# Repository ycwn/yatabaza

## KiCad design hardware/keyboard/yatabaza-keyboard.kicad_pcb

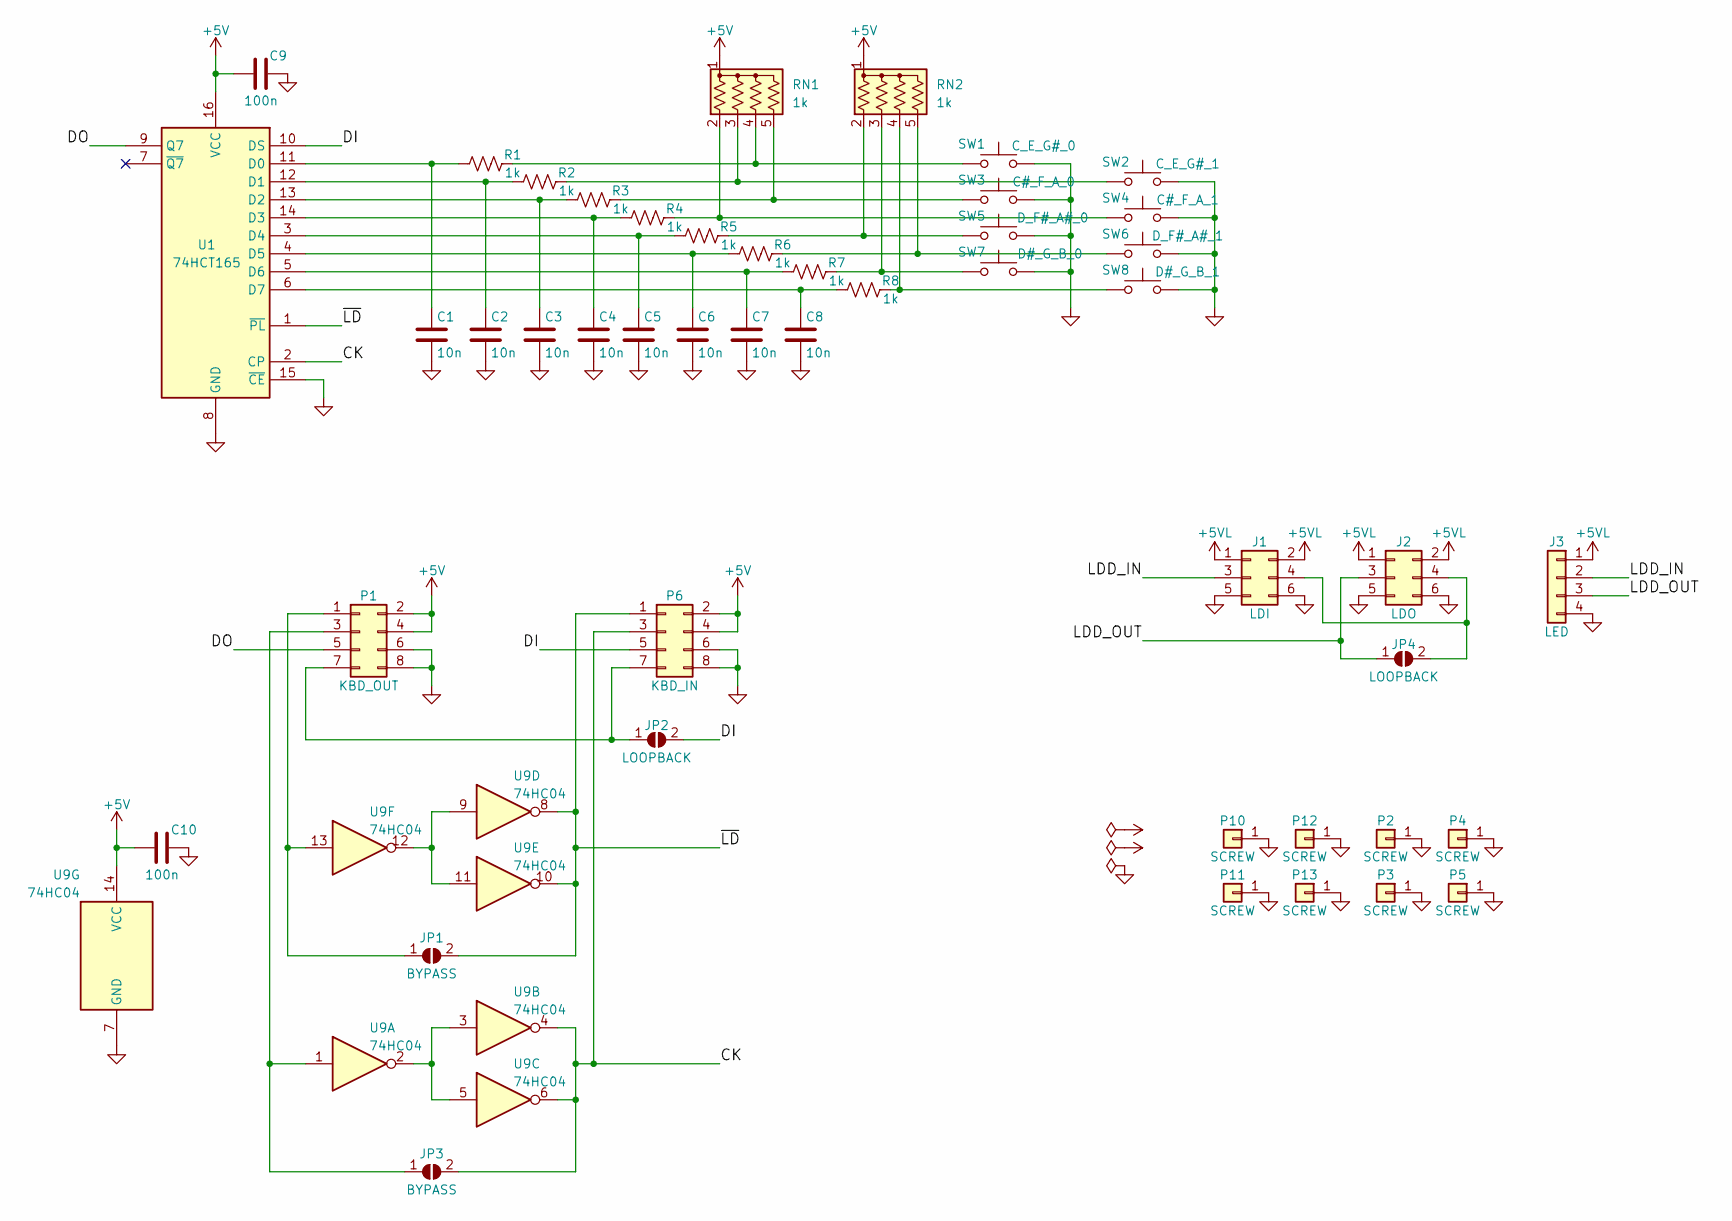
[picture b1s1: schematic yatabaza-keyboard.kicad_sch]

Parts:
C1, C2, C3, C4, C5, C6, C7, C8: 10n; C_Disc_D3.0mm_W1.6mm_P2.50mm
C9, C10: 100n; C_Disc_D3.0mm_W1.6mm_P2.50mm
J1: LDI; PinHeader_2x03_P2.54mm_Vertical
J2: LDO; PinHeader_2x03_P2.54mm_Vertical
J3: LED; PinHeader_1x04_P2.54mm_Vertical
JP1, JP3: BYPASS; SolderJumper-2_P1.3mm_Open_Pad1.0x1.5mm
JP2, JP4: LOOPBACK; SolderJumper-2_P1.3mm_Open_Pad1.0x1.5mm
P1: KBD_OUT; PinHeader_2x04_P2.54mm_Vertical
P2, P3, P4, P5, P10, P11, P12, P13: SCREW; MountingHole_3.5mm_Pad
P6: KBD_IN; PinHeader_2x04_P2.54mm_Vertical
R1, R2, R3, R4, R5, R6, R7, R8: 1k; R_Axial_DIN0204_L3.6mm_D1.6mm_P2.54mm_Vertical
RN1, RN2: 1k; R_Array_SIP5
SW1: C_E_G#_0; SW_PUSH-12mm
SW2: C_E_G#_1; SW_PUSH-12mm
SW3: C#_F_A_0; SW_PUSH-12mm
SW4: C#_F_A_1; SW_PUSH-12mm
SW5: D_F#_A#_0; SW_PUSH-12mm
SW6: D_F#_A#_1; SW_PUSH-12mm
SW7: D#_G_B_0; SW_PUSH-12mm
SW8: D#_G_B_1; SW_PUSH-12mm
U1: 74HCT165; DIP-16_W7.62mm
U9: 74HC04; DIP-14_W7.62mm

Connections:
+5V: C9.1, C10.1, P1.2, P1.4, P6.2, P6.4, RN1.1 (common), RN2.1 (common), U1.16 (VCC), U9.14 (VCC)
+5VL: J1.1, J1.2, J2.1, J2.2, J3.1
/CK: JP3.2 (B), P6.3, U1.2 (CP), U9.4, U9.6
/DI: JP2.2 (B), P6.5, U1.10 (DS)
/DO: P1.5, U1.9 (Q7)
/LDD_IN: J1.3, J3.2
/LDD_OUT: J2.3, J3.3, JP4.1 (A)
/~LD: JP1.2 (B), P6.1, U1.1 (~PL), U9.8, U9.10
GND: C1.2, C2.2, C3.2, C4.2, C5.2, C6.2, C7.2, C8.2, C9.2, C10.2, J1.5, J1.6, J2.5, J2.6, J3.4, P1.6, P1.8, P2.1, P3.1, P4.1, P5.1, P6.6, P6.8, P10.1, P11.1, P12.1, P13.1, SW1.1, SW2.1, SW3.1, SW4.1, SW5.1, SW6.1, SW7.1, SW8.1, U1.8 (GND), U1.15 (~CE), U9.7 (GND)
unnamed: C1.1, R1.2, U1.11 (D0)
unnamed: C2.1, R2.2, U1.12 (D1)
unnamed: C3.1, R3.2, U1.13 (D2)
unnamed: C4.1, R4.2, U1.14 (D3)
unnamed: C5.1, R5.2, U1.3 (D4)
unnamed: C6.1, R6.2, U1.4 (D5)
unnamed: C7.1, R7.2, U1.5 (D6)
unnamed: C8.1, R8.2, U1.6 (D7)
unnamed: J1.4, J2.4, JP4.2 (B)
unnamed: JP1.1 (A), P1.1, U9.13
unnamed: JP2.1 (A), P1.7, P6.7
unnamed: JP3.1 (A), P1.3, U9.1
unnamed: R1.1, RN1.4 (R3), SW1.2
unnamed: R2.1, RN1.3 (R2), SW2.2
unnamed: R3.1, RN1.5 (R4), SW3.2
unnamed: R4.1, RN1.2 (R1), SW4.2
unnamed: R5.1, RN2.2 (R1), SW5.2
unnamed: R6.1, RN2.5 (R4), SW6.2
unnamed: R7.1, RN2.3 (R2), SW7.2
unnamed: R8.1, RN2.4 (R3), SW8.2
unnamed: U9.2, U9.3, U9.5
unnamed: U9.9, U9.11, U9.12

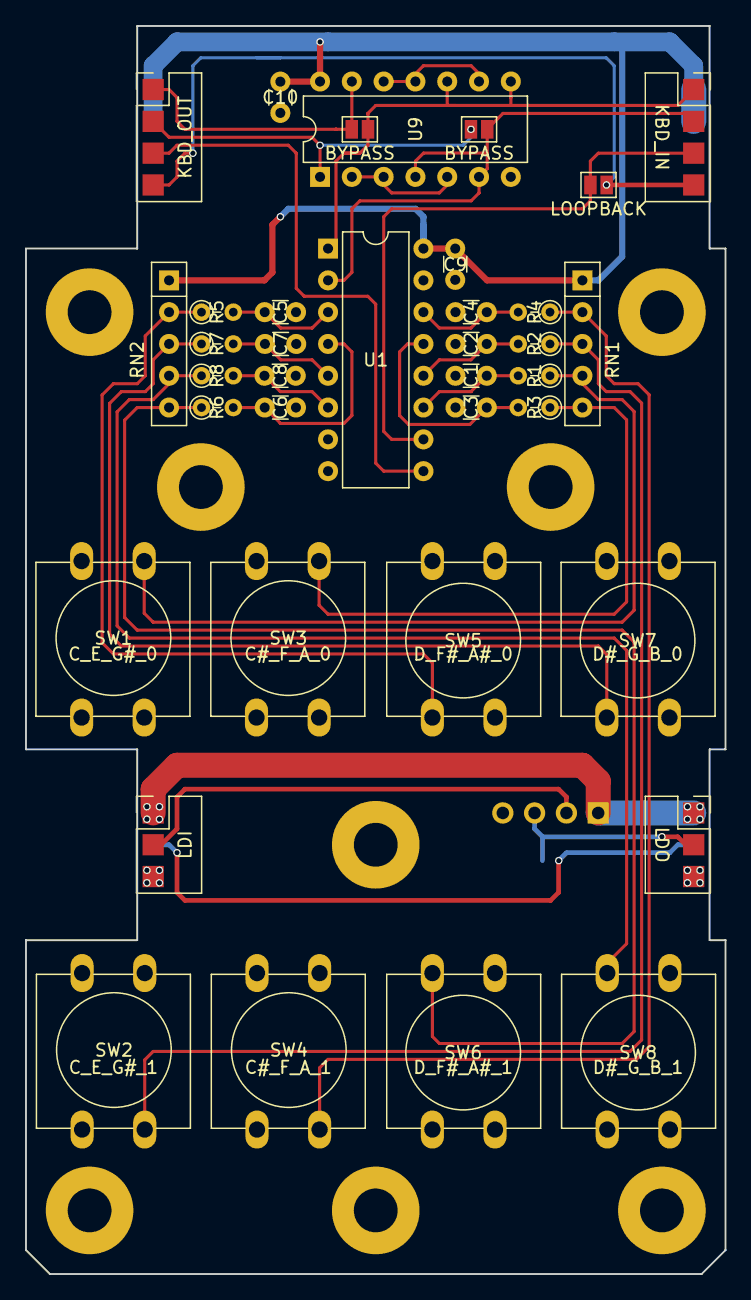
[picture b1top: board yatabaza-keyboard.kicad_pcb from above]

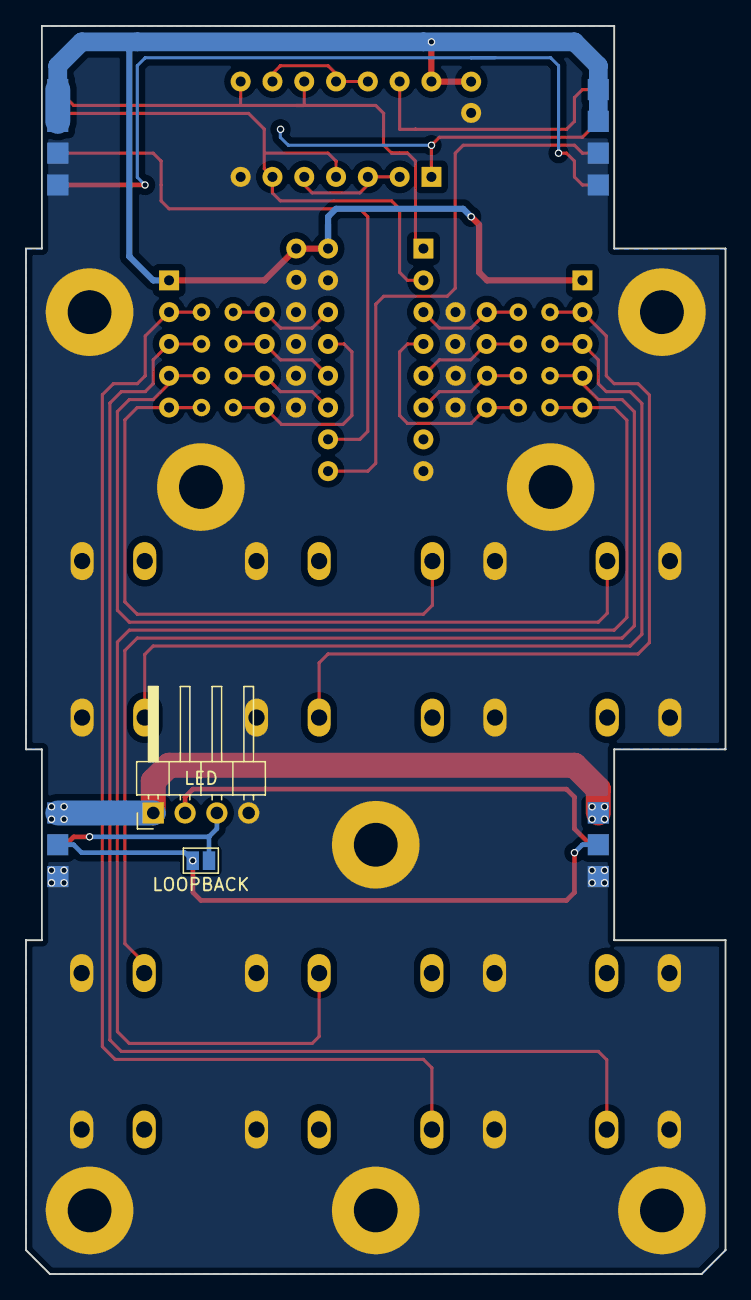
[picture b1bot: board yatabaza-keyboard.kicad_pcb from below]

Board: 2 copper layers, 55.9 x 99.7 mm, 47 parts (2 on the bottom side), 31 nets.

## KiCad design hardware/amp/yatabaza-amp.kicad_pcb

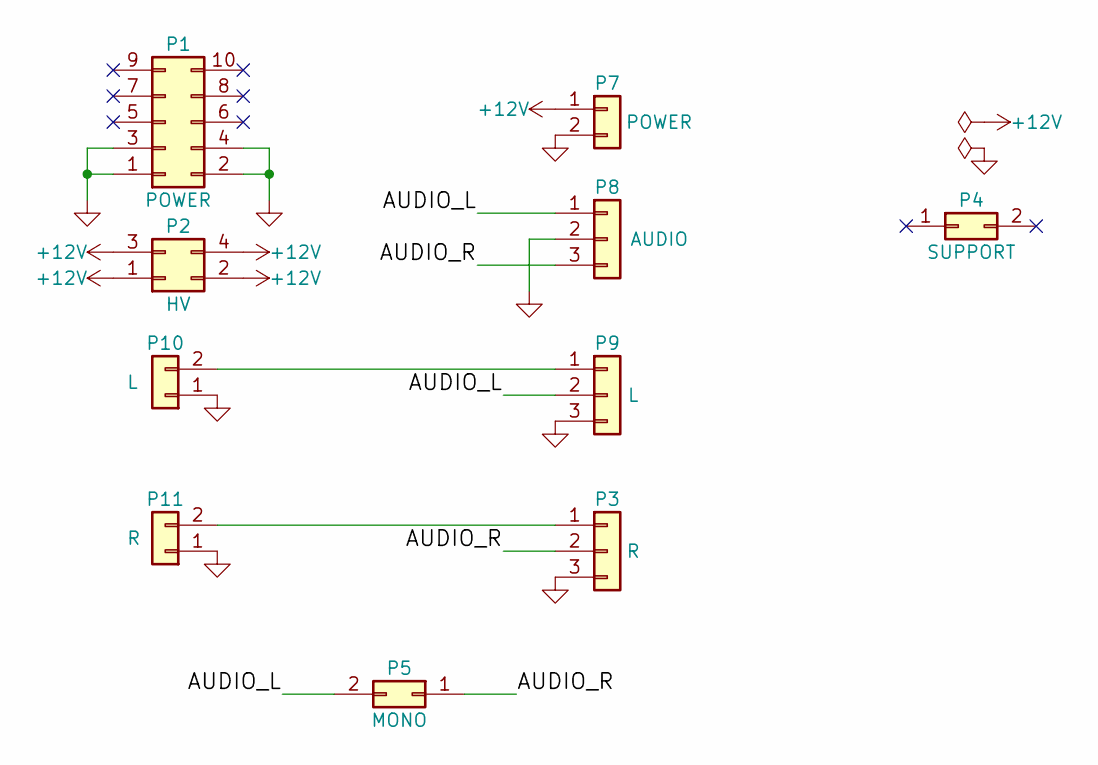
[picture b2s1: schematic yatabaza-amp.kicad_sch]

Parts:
P1: POWER; PinHeader_2x05_P2.54mm_Vertical
P2: HV; PinHeader_2x02_P2.54mm_Vertical
P3: R; PinHeader_1x03_P2.54mm_Vertical
P4: SUPPORT; PinHeader_2x01_P2.54mm_Vertical
P5: MONO; SolderJumper-2_P1.3mm_Open_Pad1.0x1.5mm
P7: POWER; PinHeader_2x01_P2.54mm_Vertical
P8: AUDIO; PinHeader_1x03_P2.54mm_Vertical
P9: L; PinHeader_1x03_P2.54mm_Vertical
P10: L; PinHeader_1x02_P2.54mm_Vertical
P11: R; PinHeader_1x02_P2.54mm_Vertical

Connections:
+12V: P2.1, P2.2, P2.3, P2.4, P7.1
/AUDIO_L: P5.2, P8.1, P9.2
/AUDIO_R: P3.2, P5.1, P8.3
GND: P1.1, P1.2, P1.3, P1.4, P3.3, P7.2, P8.2, P9.3, P10.1, P11.1
unnamed: P3.1, P11.2
unnamed: P9.1, P10.2

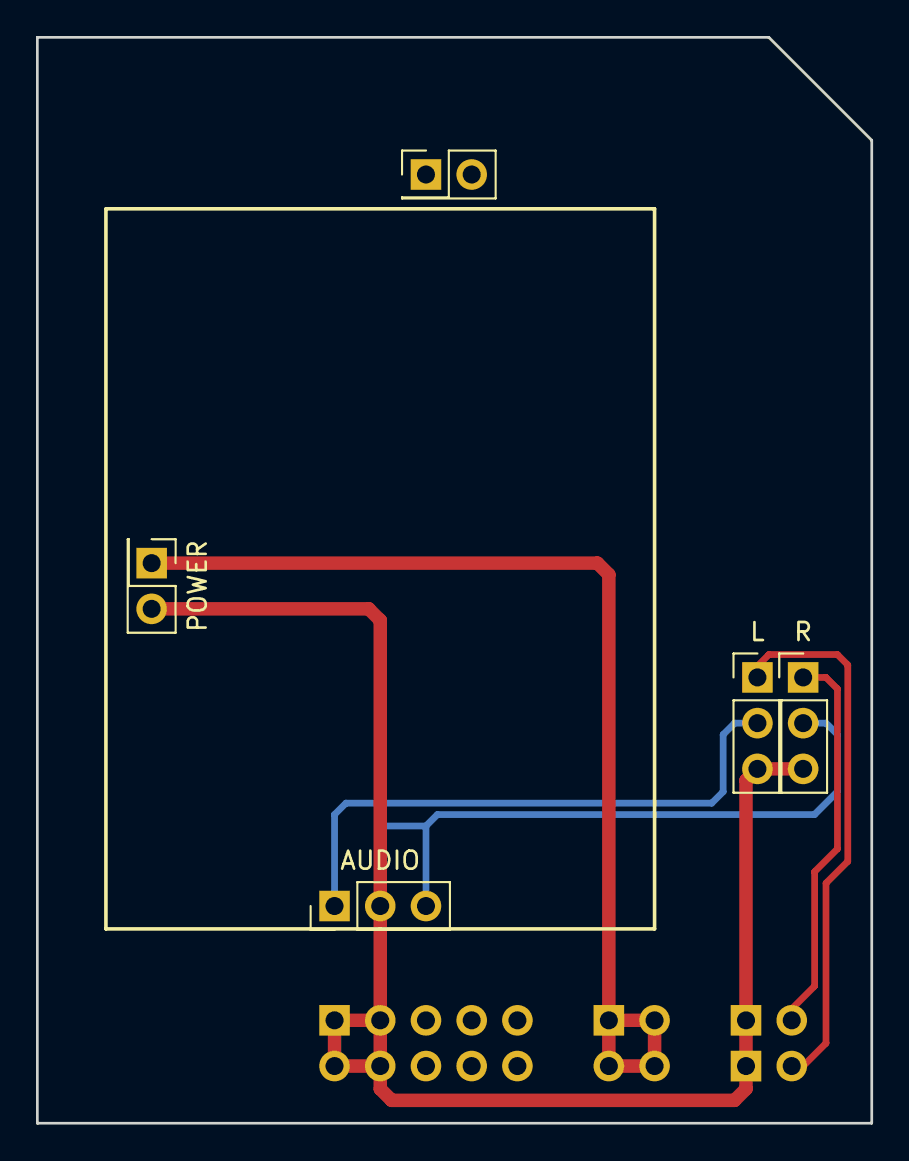
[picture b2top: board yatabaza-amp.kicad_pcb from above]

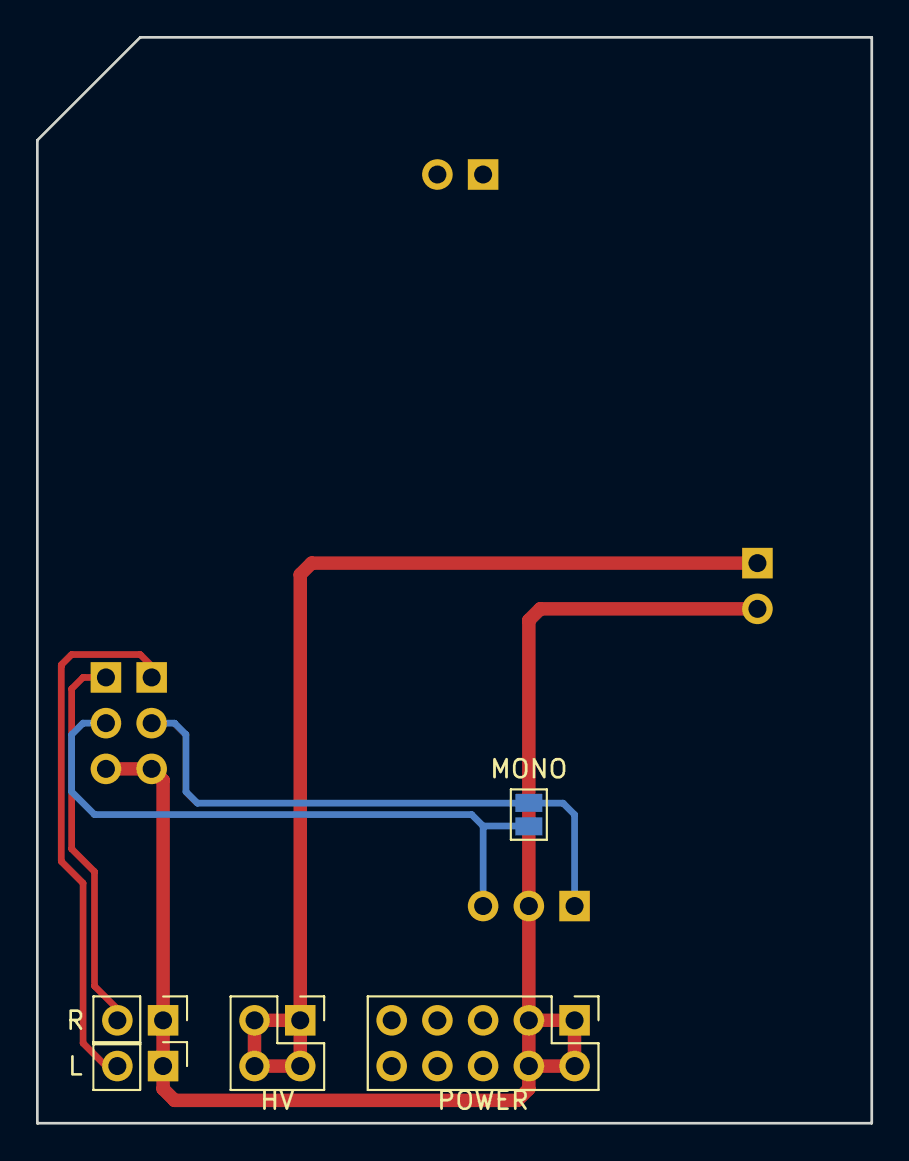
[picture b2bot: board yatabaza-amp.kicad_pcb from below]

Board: 2 copper layers, 46.4 x 60.3 mm, 10 parts (5 on the bottom side), 6 nets.

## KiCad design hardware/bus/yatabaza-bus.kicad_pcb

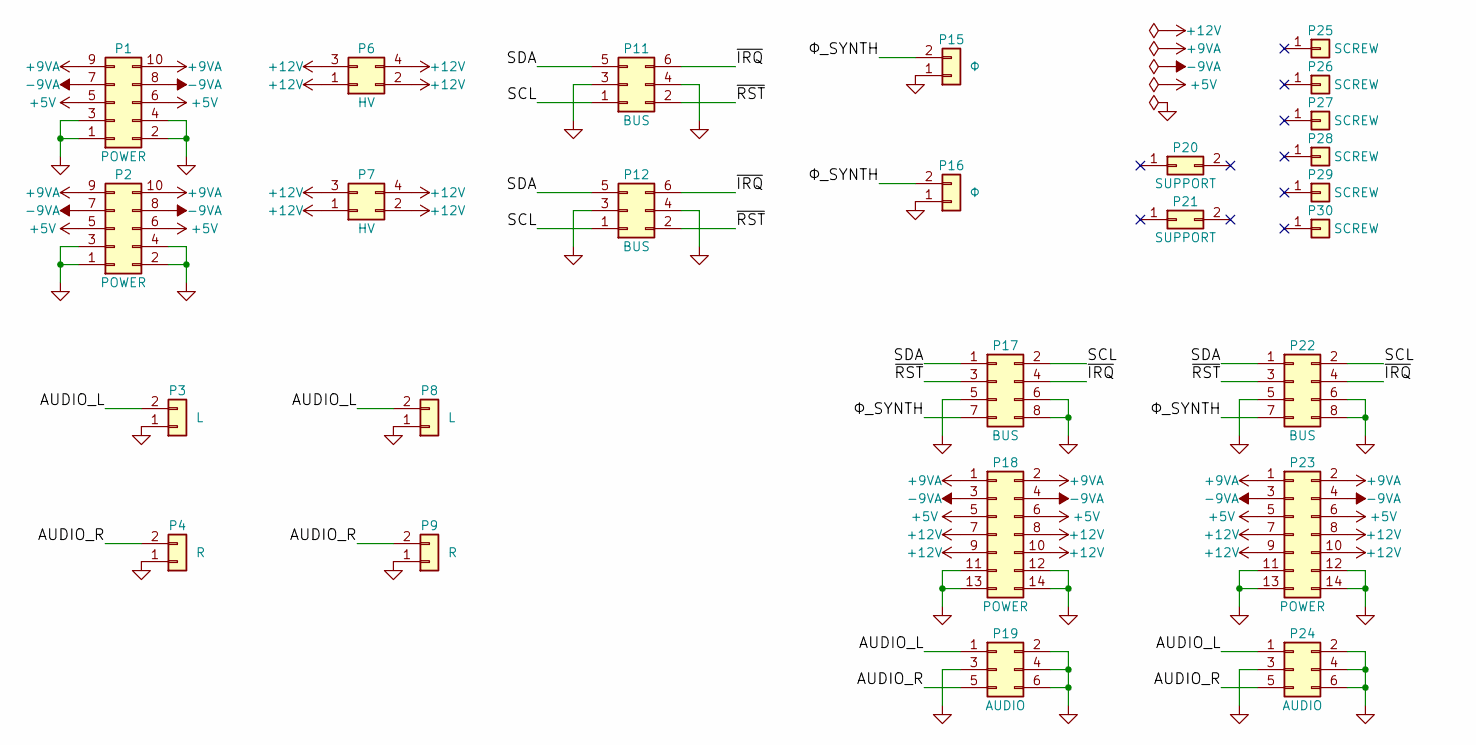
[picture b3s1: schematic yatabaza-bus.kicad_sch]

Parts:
P1, P2: POWER; PinHeader_2x05_P2.54mm_Vertical
P3, P8: L; PinHeader_1x02_P2.54mm_Vertical
P4, P9: R; PinHeader_1x02_P2.54mm_Vertical
P6, P7: HV; PinHeader_2x02_P2.54mm_Vertical
P11, P12: BUS; PinHeader_2x03_P2.54mm_Vertical
P15, P16: Φ; PinHeader_1x02_P2.54mm_Vertical
P17, P22: BUS; PinHeader_2x04_P2.54mm_Vertical
P18, P23: POWER; PinHeader_2x07_P2.54mm_Vertical
P19, P24: AUDIO; PinHeader_2x03_P2.54mm_Vertical
P20, P21: SUPPORT; PinHeader_1x02_P2.54mm_Vertical
P25, P26, P27, P28, P29, P30: SCREW; MountingHole_2.7mm_M2.5_ISO14580_Pad

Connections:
+5V: P1.5, P1.6, P2.5, P2.6, P18.5, P18.6, P23.5, P23.6
+9VA: P1.9, P1.10, P2.9, P2.10, P18.1, P18.2, P23.1, P23.2
+12V: P6.1, P6.2, P6.3, P6.4, P7.1, P7.2, P7.3, P7.4, P18.7, P18.8, P18.9, P18.10, P23.7, P23.8, P23.9, P23.10
-9VA: P1.7, P1.8, P2.7, P2.8, P18.3, P18.4, P23.3, P23.4
/AUDIO_L: P3.2, P8.2, P19.1, P24.1
/AUDIO_R: P4.2, P9.2, P19.5, P24.5
/SCL: P11.1, P12.1, P17.2, P22.2
/SDA: P11.5, P12.5, P17.1, P22.1
/~IRQ: P11.6, P12.6, P17.4, P22.4
/~RST: P11.2, P12.2, P17.3, P22.3
/Φ_SYNTH: P15.2, P16.2, P17.7, P22.7
GND: P1.1, P1.2, P1.3, P1.4, P2.1, P2.2, P2.3, P2.4, P3.1, P4.1, P8.1, P9.1, P11.3, P11.4, P12.3, P12.4, P15.1, P16.1, P17.5, P17.6, P17.8, P18.11, P18.12, P18.13, P18.14, P19.2, P19.3, P19.4, P19.6, P22.5, P22.6, P22.8, P23.11, P23.12, P23.13, P23.14, P24.2, P24.3, P24.4, P24.6

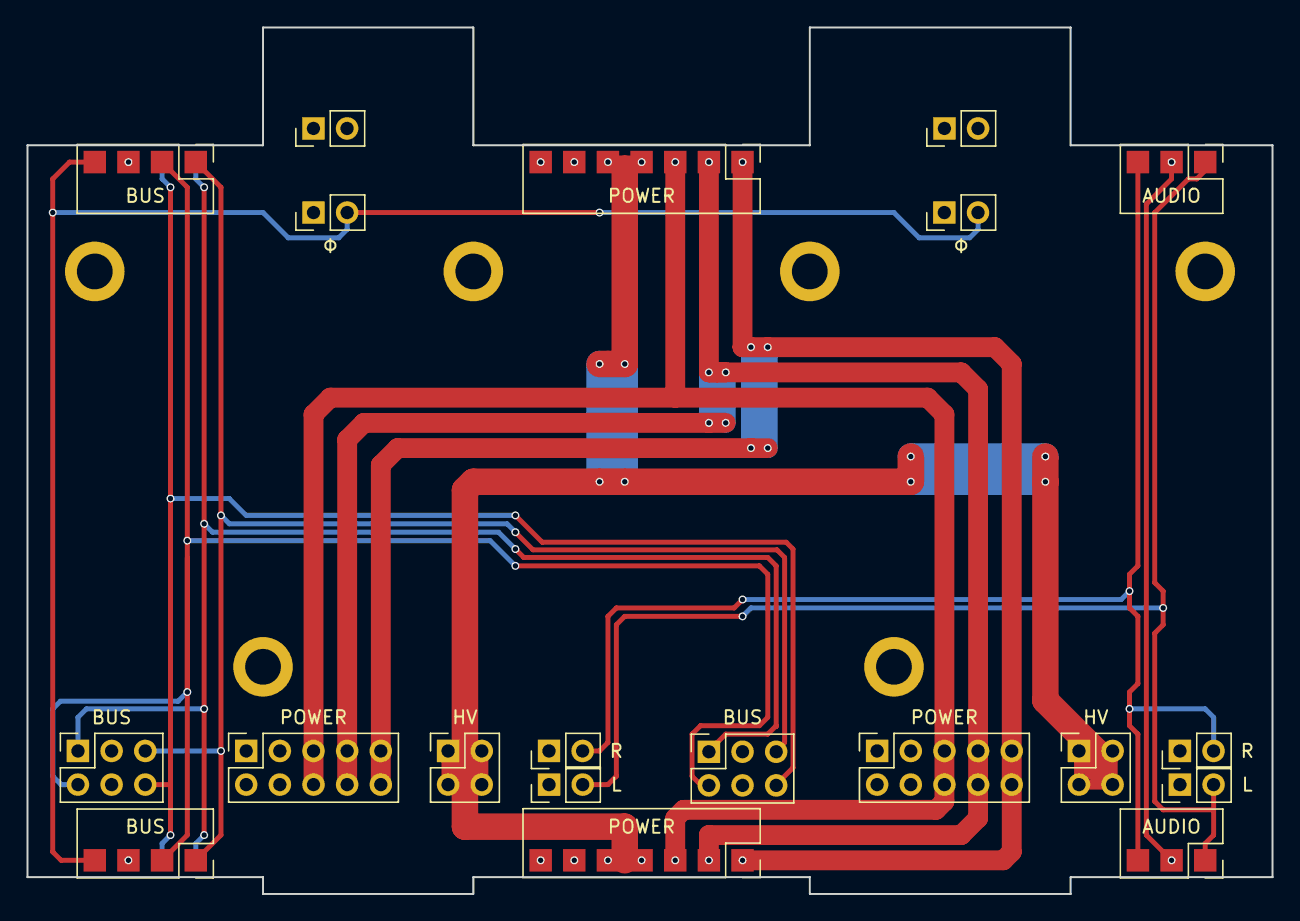
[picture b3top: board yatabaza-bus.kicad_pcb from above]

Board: 2 copper layers, 94.0 x 65.4 mm, 26 parts (0 on the bottom side), 12 nets.

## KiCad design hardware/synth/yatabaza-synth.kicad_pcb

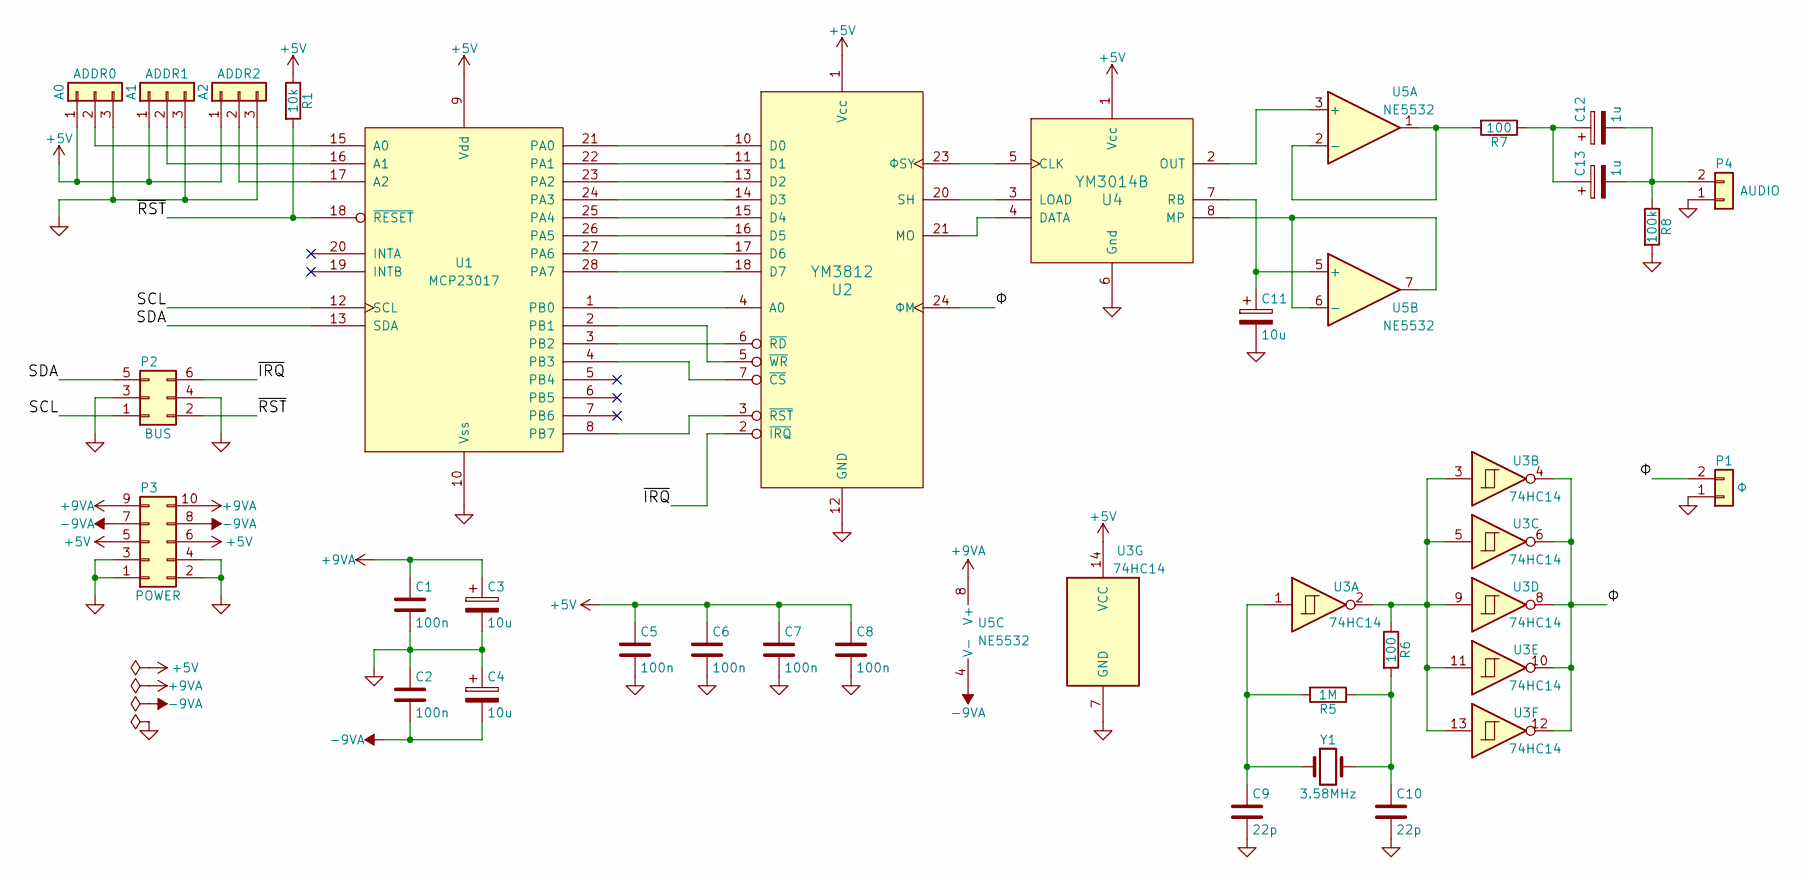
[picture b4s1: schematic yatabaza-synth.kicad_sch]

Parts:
A0: ADDR0; SolderJumper-3_P1.3mm_Open_Pad1.0x1.5mm_NumberLabels
A1: ADDR1; SolderJumper-3_P1.3mm_Open_Pad1.0x1.5mm_NumberLabels
A2: ADDR2; SolderJumper-3_P1.3mm_Open_Pad1.0x1.5mm_NumberLabels
C1, C2, C5, C6, C7, C8: 100n; C_Disc_D3.0mm_W1.6mm_P2.50mm
C3, C4, C11: 10u; CP_Radial_D5.0mm_P2.50mm
C9, C10: 22p; C_Disc_D3.0mm_W1.6mm_P2.50mm
C12, C13: 1u; CP_Radial_D5.0mm_P2.50mm
P1: Φ; PinHeader_1x02_P2.54mm_Vertical
P2: BUS; PinHeader_2x03_P2.54mm_Vertical
P3: POWER; PinHeader_2x05_P2.54mm_Vertical
P4: AUDIO; PinHeader_1x02_P2.54mm_Vertical
R1: 10k; R_Axial_DIN0204_L3.6mm_D1.6mm_P2.54mm_Vertical
R5: 1M; R_Axial_DIN0204_L3.6mm_D1.6mm_P2.54mm_Vertical
R6, R7: 100; R_Axial_DIN0204_L3.6mm_D1.6mm_P2.54mm_Vertical
R8: 100k; R_Axial_DIN0204_L3.6mm_D1.6mm_P2.54mm_Vertical
U1: MCP23017
U2: YM3812
U3: 74HC14; DIP-14_W7.62mm
U4: YM3014B
U5: NE5532; DIP-8_W7.62mm
Y1: 3.58MHz; Crystal_HC49-U_Vertical

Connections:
+5V: A0.1, A1.1, A2.1, C5.1, C6.1, C7.1, C8.1, P3.5, P3.6, R1.1, U1.9 (Vdd), U2.1 (Vcc), U3.14 (VCC), U4.1 (Vcc)
+9VA: C1.1, C3.1, P3.9, P3.10, U5.8 (V+)
-9VA: C2.2, C4.2, P3.7, P3.8, U5.4 (V-)
/SCL: P2.1, U1.12 (SCL)
/SDA: P2.5, U1.13 (SDA)
/~IRQ: P2.6, U2.2 (~IRQ)
/~RST: P2.2, R1.2, U1.18 (~RESET)
/Φ: P1.2, U2.24 (ΦM), U3.4, U3.6, U3.8, U3.10, U3.12
GND: A0.3, A1.3, A2.3, C1.2, C2.1, C3.2, C4.1, C5.2, C6.2, C7.2, C8.2, C9.2, C10.2, C11.2, P1.1, P2.3, P2.4, P3.1, P3.2, P3.3, P3.4, P4.1, R8.2, U1.10 (Vss), U2.12 (GND), U3.7 (GND), U4.6 (Gnd)
unnamed: A0.2, U1.15 (A0)
unnamed: A1.2, U1.16 (A1)
unnamed: A2.2, U1.17 (A2)
unnamed: C9.1, R5.2, U3.1, Y1.1
unnamed: C10.1, R5.1, R6.2, Y1.2
unnamed: C11.1, U4.7 (RB), U5.5 (+)
unnamed: C12.1, C13.1, R7.1
unnamed: C12.2, C13.2, P4.2, R8.1
unnamed: R6.1, U3.2, U3.3, U3.5, U3.9, U3.11, U3.13
unnamed: R7.2, U5.1, U5.2 (-)
unnamed: U1.1 (PB0), U2.4 (A0)
unnamed: U1.2 (PB1), U2.5 (~WR)
unnamed: U1.3 (PB2), U2.6 (~RD)
unnamed: U1.4 (PB3), U2.7 (~CS)
unnamed: U1.8 (PB7), U2.3 (~RST)
unnamed: U1.21 (PA0), U2.10 (D0)
unnamed: U1.22 (PA1), U2.11 (D1)
unnamed: U1.23 (PA2), U2.13 (D2)
unnamed: U1.24 (PA3), U2.14 (D3)
unnamed: U1.25 (PA4), U2.15 (D4)
unnamed: U1.26 (PA5), U2.16 (D5)
unnamed: U1.27 (PA6), U2.17 (D6)
unnamed: U1.28 (PA7), U2.18 (D7)
unnamed: U2.20 (SH), U4.3 (LOAD)
unnamed: U2.21 (MO), U4.4 (DATA)
unnamed: U2.23 (ΦSY), U4.5 (CLK)
unnamed: U4.2 (OUT), U5.3 (+)
unnamed: U4.8 (MP), U5.6 (-), U5.7

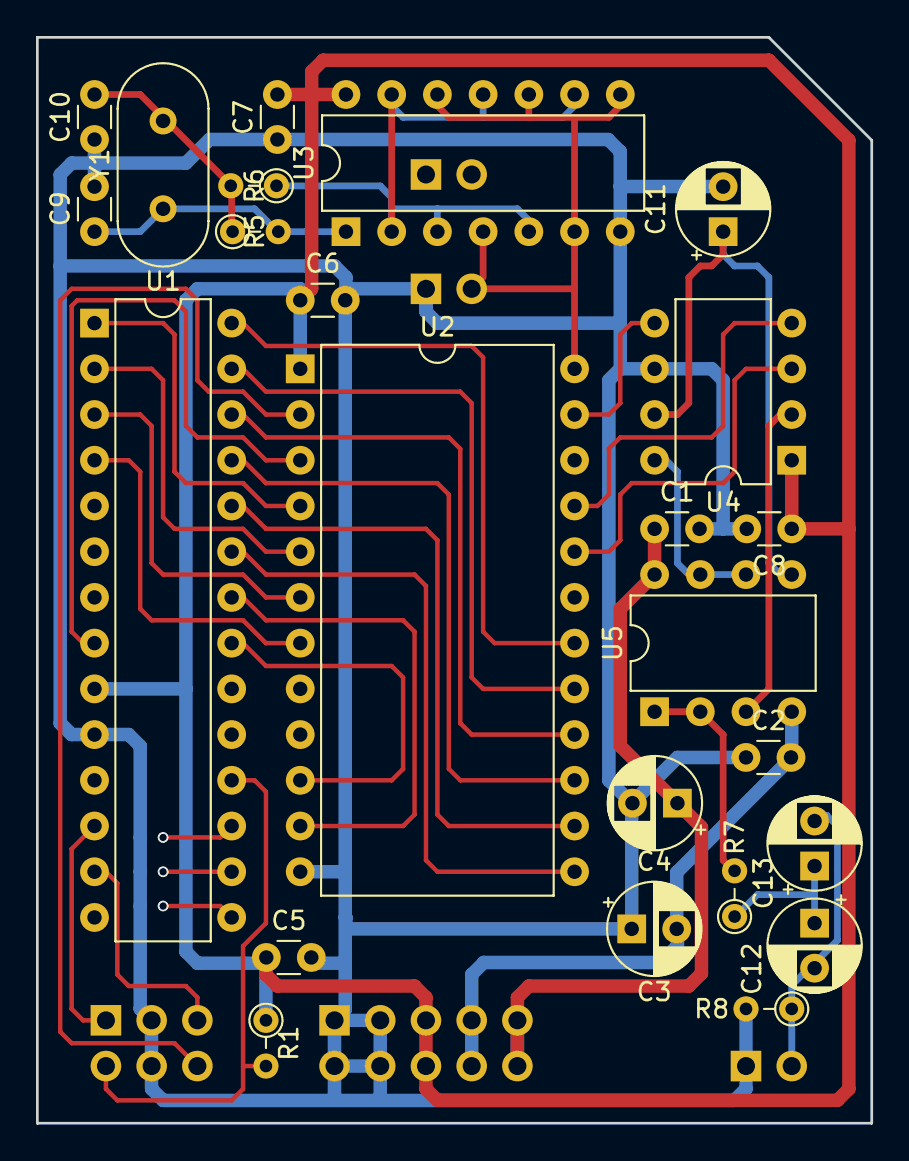
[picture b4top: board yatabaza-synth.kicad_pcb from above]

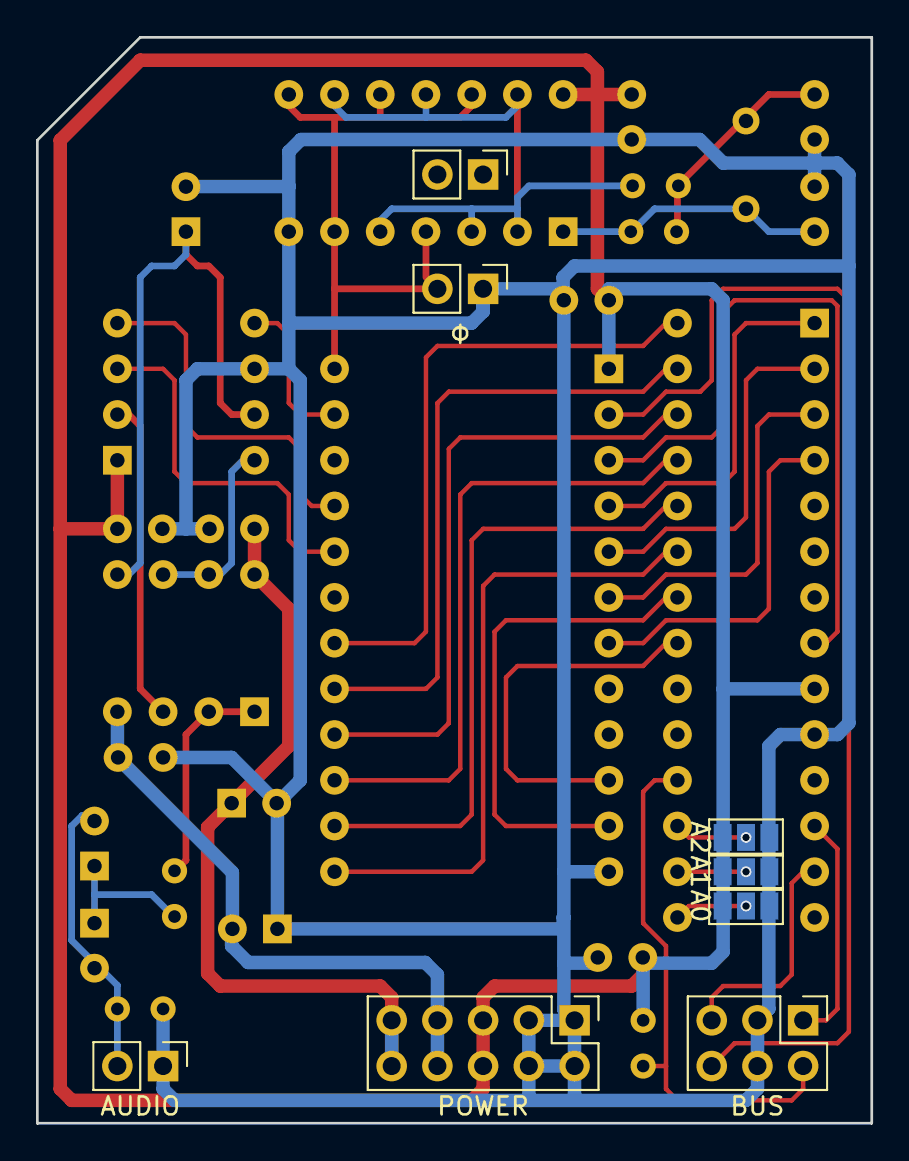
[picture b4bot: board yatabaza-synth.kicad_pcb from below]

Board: 2 copper layers, 46.4 x 60.3 mm, 31 parts (7 on the bottom side), 37 nets.

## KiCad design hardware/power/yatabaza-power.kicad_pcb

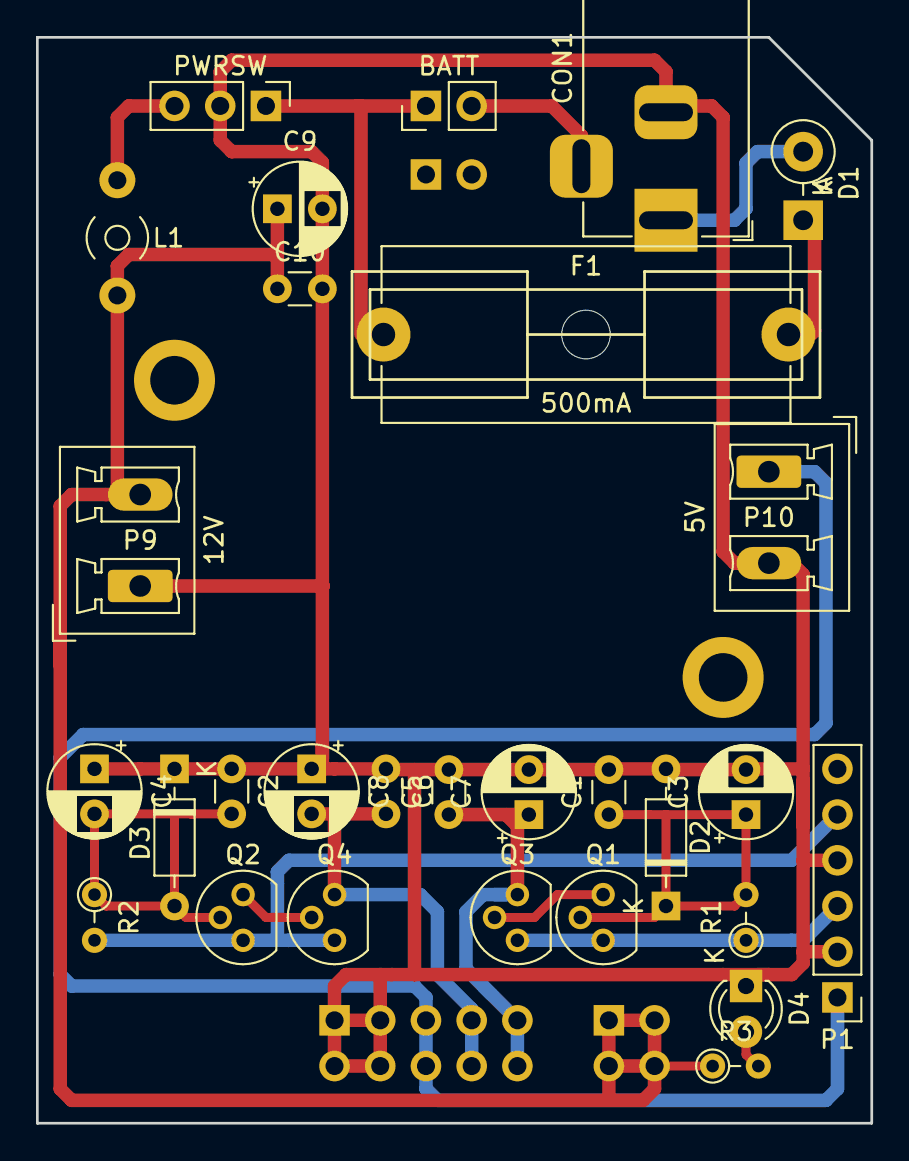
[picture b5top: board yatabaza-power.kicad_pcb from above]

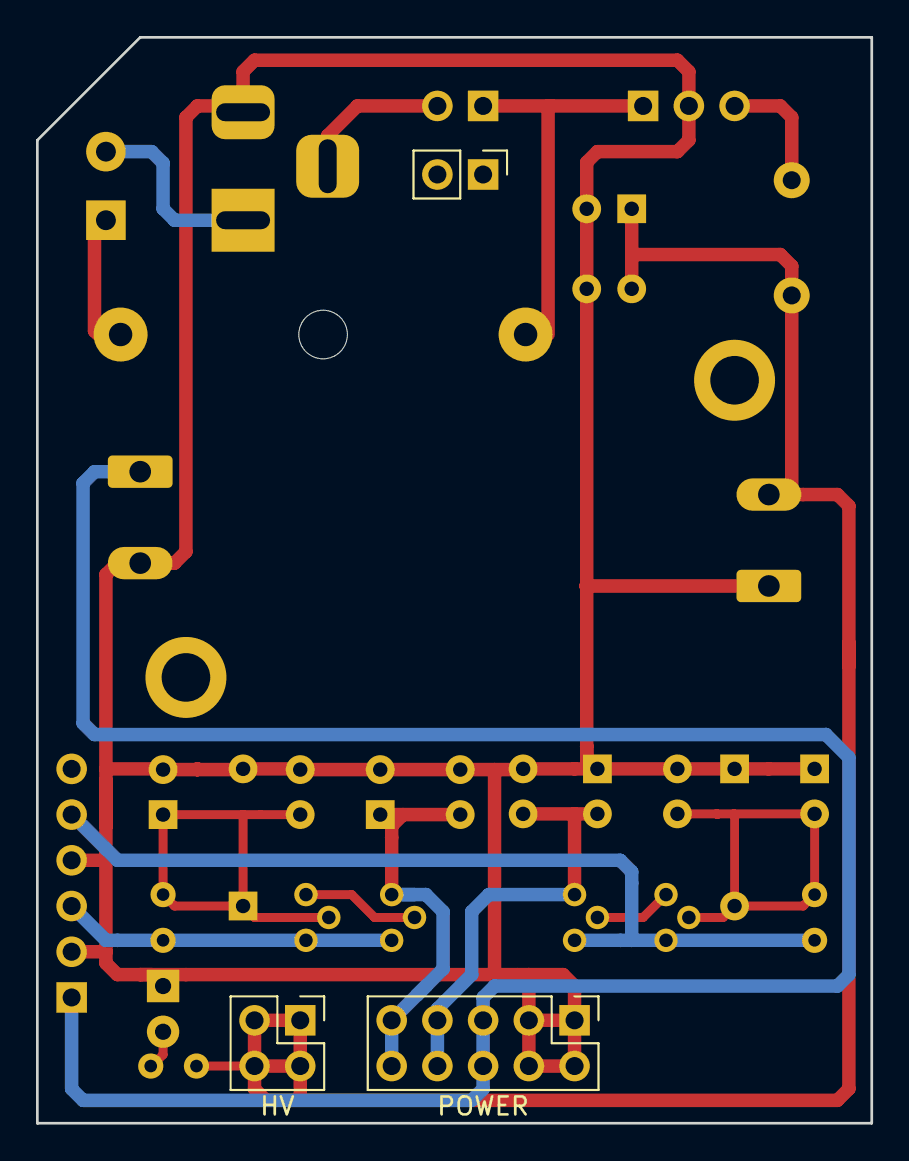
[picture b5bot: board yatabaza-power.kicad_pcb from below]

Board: 2 copper layers, 46.4 x 60.3 mm, 34 parts (3 on the bottom side), 17 nets.

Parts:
C1, C2, C5, C6, C10: 100n; C_Disc_D3.0mm_W1.6mm_P2.50mm
C3, C4, C7, C8, C9: 100u; CP_Radial_D5.0mm_P2.50mm
CON1: POWER; BarrelJack_Horizontal
D1: 1n4007; D_DO-41_SOD81_P3.81mm_Vertical_KathodeUp
D2, D3: 12V; D_DO-35_SOD27_P7.62mm_Horizontal
D4: LED; LED_D3.0mm
F1: 500mA; Fuseholder_Cylinder-5x20mm_Schurter_0031_8201_Horizontal_Op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
L1: 100uH; L_Toroid_Horizontal_D3.2mm_P6.40mm_Diameter3-5mm_Amidon-T12
P1: DCDC_DUAL; PinHeader_1x06_P2.54mm_Vertical
P2: BATT; PinHeader_1x02_P2.54mm_Vertical
P3: PWRSW; PinHeader_1x03_P2.54mm_Vertical
P4: POWER; PinHeader_2x05_P2.54mm_Vertical
P5: HV; PinHeader_2x02_P2.54mm_Vertical
P6: SUPPORT; PinHeader_1x02_P2.54mm_Vertical
P7, P8: SCREW; MountingHole_2.7mm_M2.5_ISO14580_Pad
P9: 12V; PhoenixContact_MCV_1,5_2-G-5.08_1x02_P5.08mm_Vertical
P10: 5V; PhoenixContact_MCV_1,5_2-G-5.08_1x02_P5.08mm_Vertical
Q1, Q3: BC338; TO-92
Q2, Q4: BC328; TO-92
R1, R2, R3: 1k; R_Axial_DIN0204_L3.6mm_D1.6mm_P2.54mm_Vertical

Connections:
+5V: P1.1, P4.5, P4.6, P10.1
+9VA: C5.1, C7.1, P4.9, P4.10, Q3.3 (E)
+12V: C9.1, C10.1, L1.2, P5.1, P5.2, P5.3, P5.4, P9.2, R3.1
-9VA: C6.2, C8.2, P4.7, P4.8, Q4.3 (E)
GND: C1.2, C2.1, C3.2, C4.1, C5.2, C6.1, C7.2, C8.1, C9.2, C10.2, CON1.2, D2.2 (A), D3.1 (K), D4.1 (K), P1.2, P1.4, P3.2, P4.1, P4.2, P4.3, P4.4, P9.1, P10.2
unnamed: C1.1, C3.1, D2.1 (K), Q1.2 (B), R1.2
unnamed: C2.2, C4.2, D3.2 (A), Q2.2 (B), R2.1
unnamed: CON1.1, D1.2 (A)
unnamed: CON1.3, P2.2
unnamed: D1.1 (K), F1.1
unnamed: P1.3, Q1.1 (C), Q3.1 (C), R1.1
unnamed: P1.5, Q2.1 (C), Q4.1 (C), R2.2
unnamed: F1.2, P2.1, P3.1
unnamed: L1.1, P3.3
unnamed: Q2.3 (E), Q4.2 (B)
unnamed: Q1.3 (E), Q3.2 (B)
unnamed: D4.2 (A), R3.2
